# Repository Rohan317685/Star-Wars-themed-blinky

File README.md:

# Star-Wars-themed-blinky
This is a Star Wars themed 555 Blinky made for HackClub!

Hack Club is a 501(c)(3) non-profit that helps teens make things. For more info, go to [hackclub.com](https://hackclub.com).

This project PCB costs $3.50 and the customs and duties may defer depending on where you live!

To order the PCB go to JLPCB's official website which I find is the cheapest and most reliable company to order PCB's from!

Make an account and upload the zip files of the Gerber in the production files folder!

It should lead you to this page and it should show this after you uploaded! (It may be green you can change the color!)

You dont need pcba considering this is very simple to solder and keeps costs low! All you need to change is the color of your pcb if you want and then you should be ready to order!

Here is the schematic and the PCB of the blinky:

Here is what it looks like in the 3d viewer:

I unfortunately don't have a BOM for the parts since I'm getting a kit for the parts however I recommend LCSC and Digikey as they're the cheapest and most reliable suppliers for these types of parts!

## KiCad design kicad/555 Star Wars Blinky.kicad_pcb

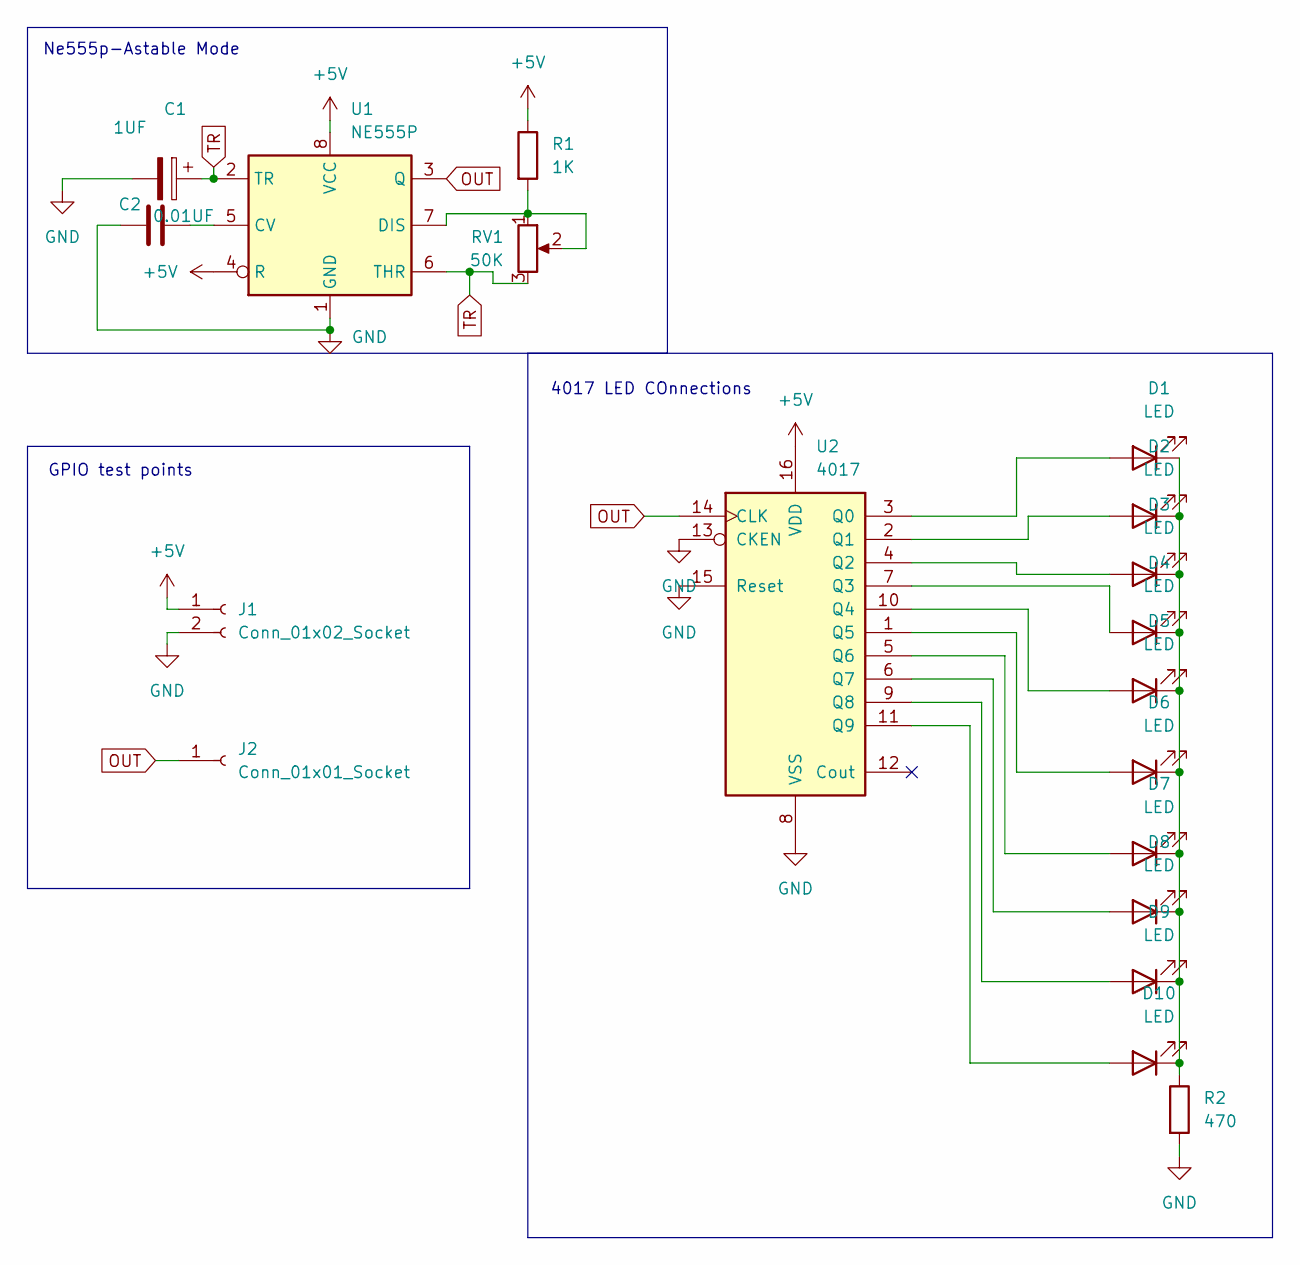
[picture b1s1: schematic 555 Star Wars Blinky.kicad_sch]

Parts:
C1: 1UF; CP_Radial_D5.0mm_P2.00mm
C2: 0.01UF; C_Disc_D7.5mm_W2.5mm_P5.00mm
D1, D2, D3, D4, D5, D6, D7, D8, D9, D10: LED; LED_D3.0mm
J1: Conn_01x02_Socket; PinHeader_1x02_P2.54mm_Vertical
J2: Conn_01x01_Socket; PinHeader_1x01_P2.54mm_Vertical
R1: 1K; R_Axial_DIN0207_L6.3mm_D2.5mm_P7.62mm_Horizontal
R2: 470; R_Axial_DIN0207_L6.3mm_D2.5mm_P7.62mm_Horizontal
RV1: 50K; Potentiometer_Vishay_T93YA_Vertical
U1: NE555P; DIP-8_W7.62mm
U2: 4017; N16

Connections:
+5V: J1.1, R1.1, U1.4 (R), U1.8 (VCC), U2.16 (VDD)
GND: C1.2, C2.2, J1.2, R2.2, U1.1 (GND), U2.8 (VSS), U2.13 (CKEN), U2.15 (Reset)
unnamed: D1.2 (A), U2.3 (Q0)
unnamed: D1.1 (K), D2.1 (K), D3.1 (K), D4.1 (K), D5.1 (K), D6.1 (K), D7.1 (K), D8.1 (K), D9.1 (K), D10.1 (K), R2.1
unnamed: D2.2 (A), U2.2 (Q1)
unnamed: D3.2 (A), U2.4 (Q2)
unnamed: D4.2 (A), U2.7 (Q3)
unnamed: D5.2 (A), U2.10 (Q4)
unnamed: D6.2 (A), U2.1 (Q5)
unnamed: D7.2 (A), U2.5 (Q6)
unnamed: D8.2 (A), U2.6 (Q7)
unnamed: D9.2 (A), U2.9 (Q8)
unnamed: D10.2 (A), U2.11 (Q9)
unnamed: C2.1, U1.5 (CV)
unnamed: R1.2, RV1.1, RV1.2, U1.7 (DIS)
OUT: J2.1, U1.3 (Q), U2.14 (CLK)
TR: C1.1, RV1.3, U1.2 (TR), U1.6 (THR)

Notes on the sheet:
4017 LED COnnections
Ne555p-Astable Mode
GPIO test points

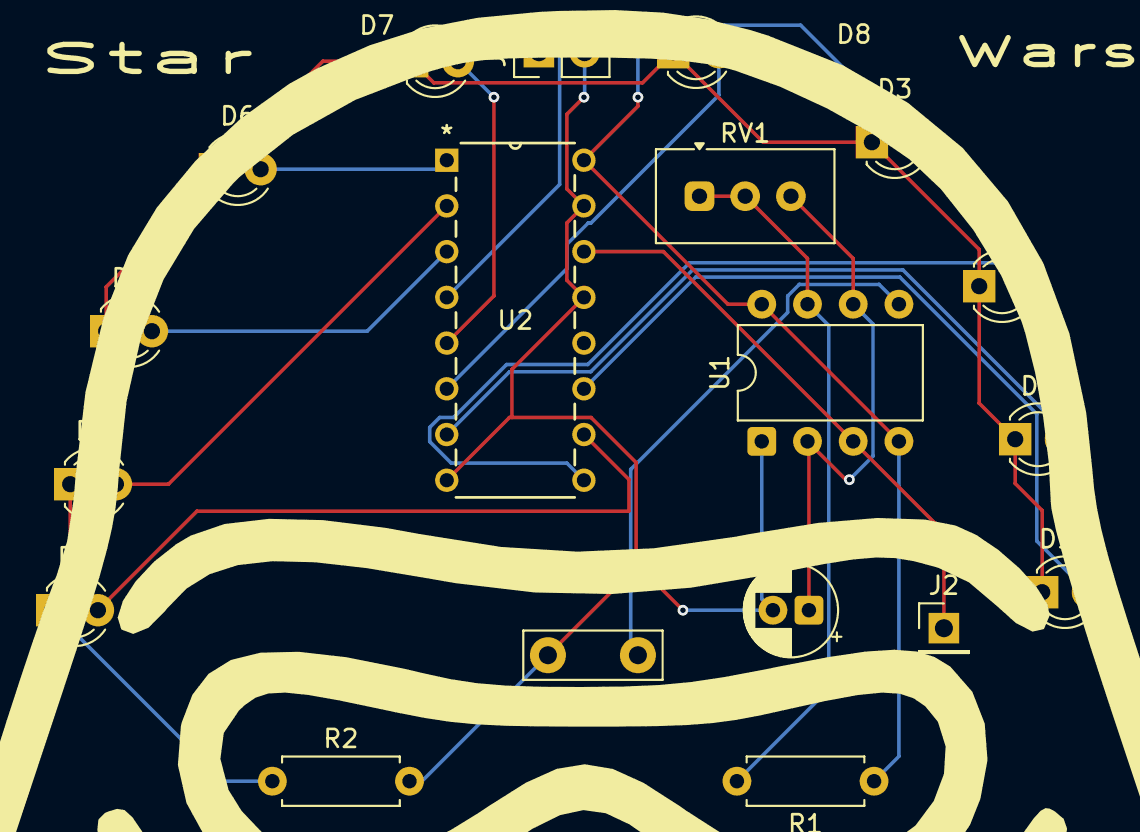
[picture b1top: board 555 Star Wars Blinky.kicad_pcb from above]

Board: 2 copper layers, 19 parts (0 on the bottom side), 17 nets.

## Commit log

2026-03-26 Create test
2026-03-26 Adding PCB files!
2026-03-26 Create placeholder
2026-03-31 Update README with project details and images
    Added detailed project information, ordering instructions, and images for the Star Wars themed 555 Blinky.
